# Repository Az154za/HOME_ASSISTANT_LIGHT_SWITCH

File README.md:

# HOME_ASSISTANT_LIGHT_SWITCH
# Description : 
  This project is made to automate , optimize and monitor house temperature , motion , toggle on and off lights via two servo motors , DHT11 for temperature sensor and motion sensor light toggling automatic with home assistant os 
# SCHEMATIC

# ROUTING

# 3D overview

# 3D case overview

# FULL 3D overview 

# BOM
| Component Name | Provider | Quantity | Price | Link |
|---|---|---|---|---|
| ELEGOO ESP32 Development Board + Terminal Adapter | Amazon.fr (ELEGOO) | 2 | $19.50 | [amazon.fr](https://www.amazon.fr/ELEGOO-D%C3%A9veloppement-Adaptateur-Terminal-Ensembles/dp/B0D8T5P8JM) |
| PCB | JLCPCB | 5 | $6.60 | - |
| SG90 180° Servo Motor | AliExpress | 4 | $6.17 | [aliexpress.com](https://fr.aliexpress.com/item/1005010199020431.html) |
| DHT11 Temperature & Humidity Sensor | AliExpress | 1 | $0.84 | [aliexpress.com](https://fr.aliexpress.com/item/1005008659347359.html) |
| PIR Motion Sensor | AliExpress | 1 | $1.07 | [aliexpress.com](https://fr.aliexpress.com/item/1005010179334039.html) |
| **TOTAL** | | | **$34.18** | |
# Dimensions of inner box

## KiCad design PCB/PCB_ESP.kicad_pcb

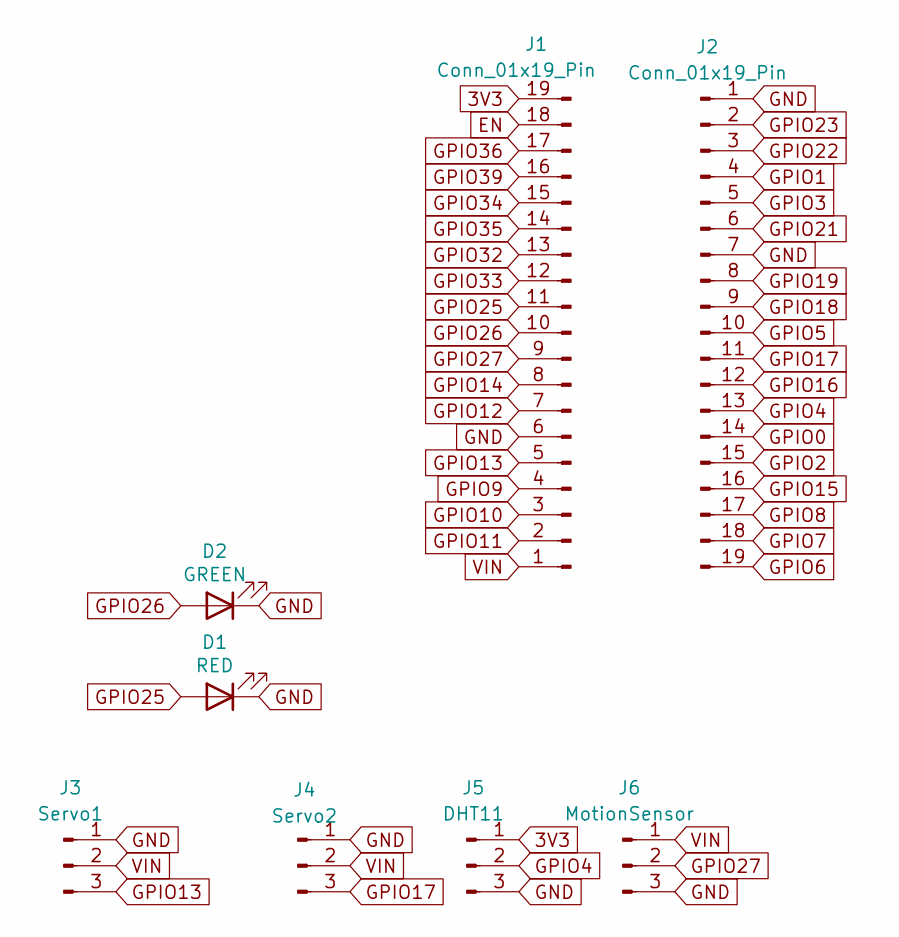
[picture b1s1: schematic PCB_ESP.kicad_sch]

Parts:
D1: RED; LED_D5.0mm
D2: GREEN; LED_D5.0mm
J1, J2: Conn_01x19_Pin; PinHeader_1x19_P2.54mm_Vertical
J3: Servo1; PinHeader_1x03_P2.54mm_Vertical
J4: Servo2; PinHeader_1x03_P2.54mm_Vertical
J5: DHT11; PinHeader_1x03_P2.54mm_Vertical
J6: MotionSensor; PinHeader_1x03_P2.54mm_Vertical

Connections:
3V3: J1.19, J5.1
EN: J1.18
GND: D1.1 (K), D2.1 (K), J1.6, J2.1, J2.7, J3.1, J4.1, J5.3, J6.3
GPIO0: J2.14
GPIO1: J2.4
GPIO2: J2.15
GPIO3: J2.5
GPIO4: J2.13, J5.2
GPIO5: J2.10
GPIO6: J2.19
GPIO7: J2.18
GPIO8: J2.17
GPIO9: J1.4
GPIO10: J1.3
GPIO11: J1.2
GPIO12: J1.7
GPIO13: J1.5, J3.3
GPIO14: J1.8
GPIO15: J2.16
GPIO16: J2.12
GPIO17: J2.11, J4.3
GPIO18: J2.9
GPIO19: J2.8
GPIO21: J2.6
GPIO22: J2.3
GPIO23: J2.2
GPIO25: D1.2 (A), J1.11
GPIO26: D2.2 (A), J1.10
GPIO27: J1.9, J6.2
GPIO32: J1.13
GPIO33: J1.12
GPIO34: J1.15
GPIO35: J1.14
GPIO36: J1.17
GPIO39: J1.16
VIN: J1.1, J3.2, J4.2, J6.1

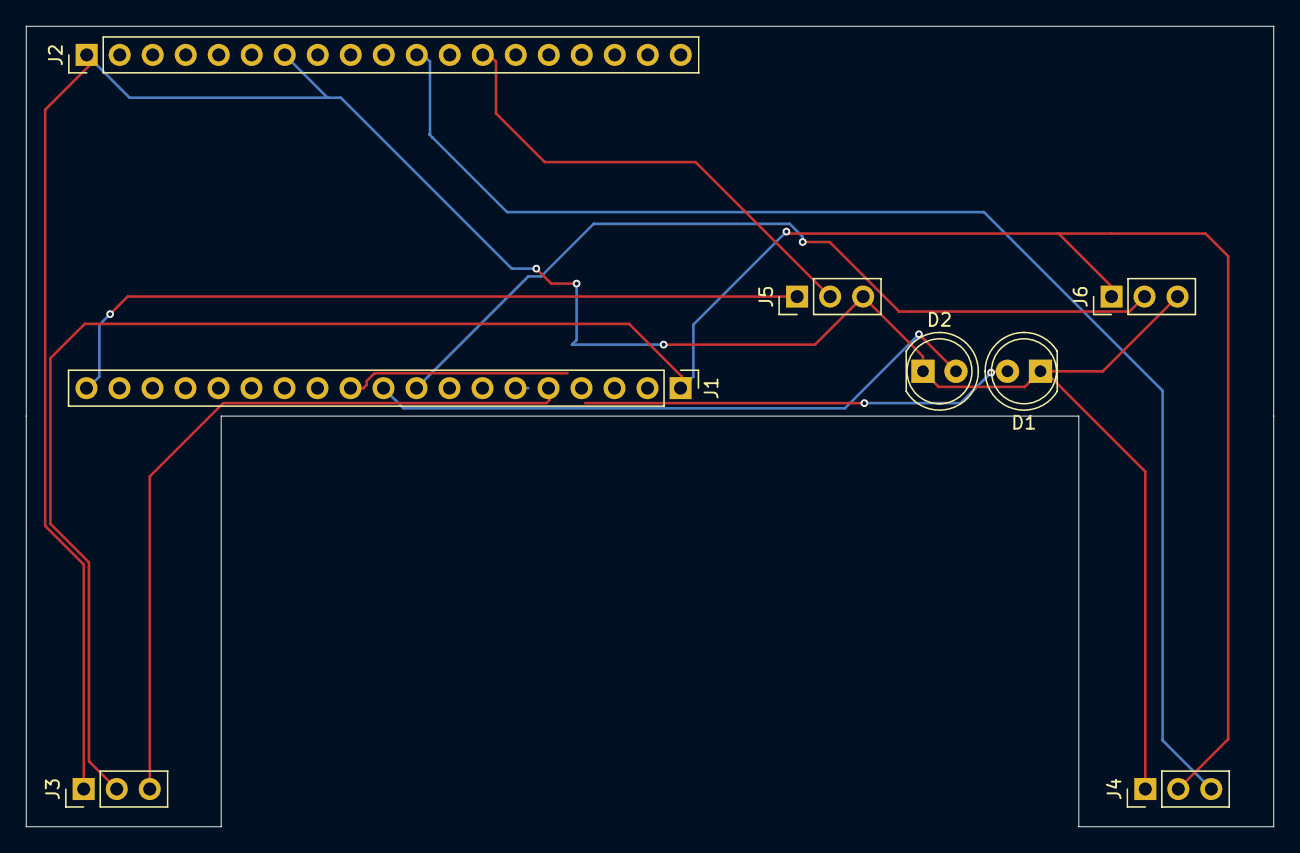
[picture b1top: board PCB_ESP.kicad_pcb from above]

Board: 2 copper layers, 96.0 x 61.6 mm, 8 parts (0 on the bottom side), 9 nets.

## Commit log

2026-03-01 Add dimensions section and image to README
2026-03-01 Add BOM section to README with component details
    Added a Bill of Materials (BOM) section with component details.
2026-03-01 Add BOM.csv with component details and pricing
